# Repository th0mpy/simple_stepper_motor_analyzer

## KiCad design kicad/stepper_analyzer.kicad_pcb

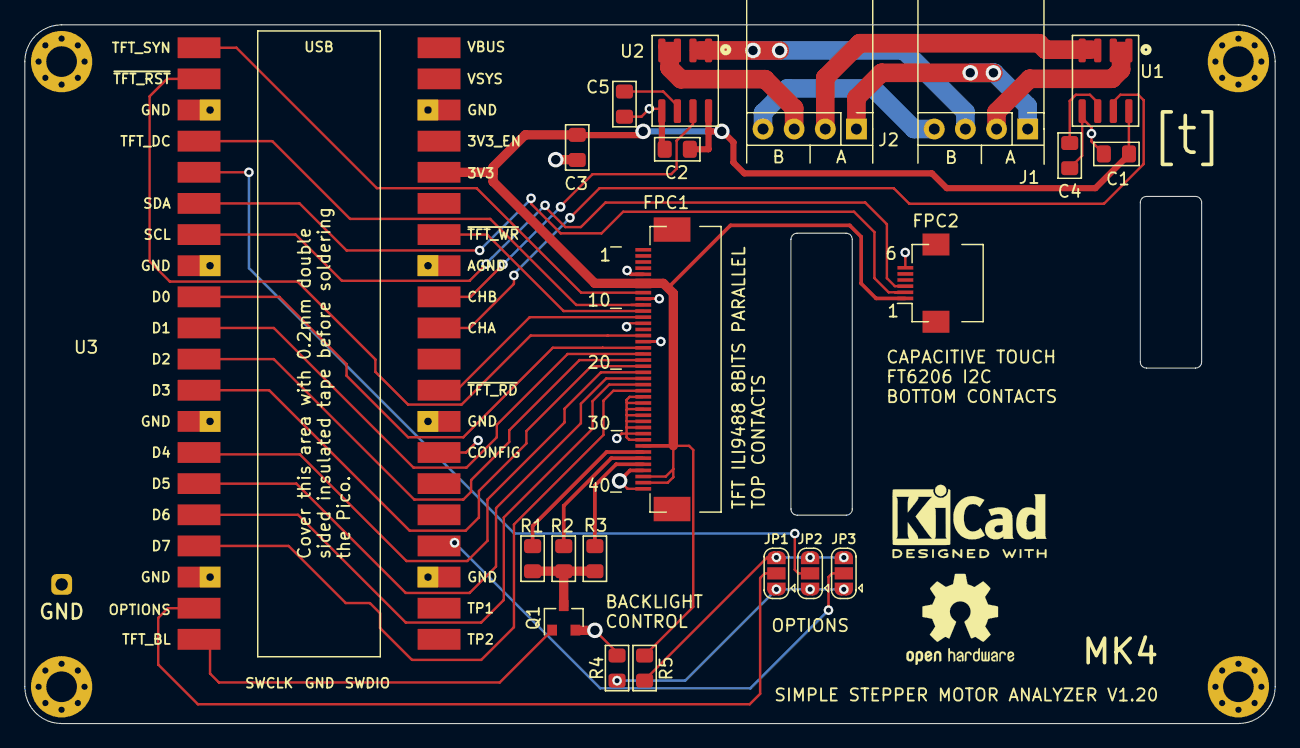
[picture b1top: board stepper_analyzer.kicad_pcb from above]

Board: 2 copper layers, 102.0 x 57.0 mm, 28 parts (1 on the bottom side), 37 nets.

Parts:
C1, C2: 0.1u; C_0805_2012Metric_Pad1.15x1.40mm_HandSolder
C3: 10u; C_0805_2012Metric_Pad1.15x1.40mm_HandSolder
C4: 1nf; C_0805_2012Metric_Pad1.15x1.40mm_HandSolder
C5: DNP; C_0805_2012Metric_Pad1.15x1.40mm_HandSolder
FPC1: Connector_Conn_01x40_Female; JUSHUO-AFC07-S40ECC-00_40P_05mm_flipped
FPC2: FPC connector, 6 pins, 0.5mm, BOTTOM contacts; JUSHUO-AFC01-S06FCC-00_6p_05mm
H1, H2, H3, H4: MountingHole; MountingHole_2.5mm_Pad_Via
J1, J2: Connector_Conn_01x04_Male; connector_4pins_horizontal
JP1: OPTION1; SolderJumper-3_P1.3mm_Open_RoundedPad1.0x1.5mm
JP2: OPTION2; SolderJumper-3_P1.3mm_Open_RoundedPad1.0x1.5mm
JP3: OPTION3; SolderJumper-3_P1.3mm_Open_RoundedPad1.0x1.5mm
LOGO1: Logo_Open_Hardware_Small; OSHW-Logo2_9.8x8mm_SilkScreen
M1: Motor; null_footprint
Q1: AO3400A; SOT-23
R1, R2, R3: 8R2; R_0805_2012Metric_Pad1.15x1.40mm_HandSolder
R4: 1K; R_0805_2012Metric_Pad1.15x1.40mm_HandSolder
R5: 1K; R_0805_2012Metric_Pad1.15x1.40mm_HandSolder_no_3d
TP3: TestPoint; testpoint_double_side
U1, U2: (CURRENT SENSOR); SOIC-8_3.9x4.9mm_P1.27mm
U3: Pico; Pico_smd_dedicated

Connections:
+3V3: C1.2, C2.2, C3.2, FPC1.6, FPC1.7, FPC1.33, FPC1.38, FPC1.39, FPC2.1, R5.2, U1.8, U2.8, U3.36
/CHA: U1.7, U3.31
/CHB: U2.7, U3.32
/D0: FPC1.17, U3.9
/D1: FPC1.18, U3.10
/D2: FPC1.19, U3.11
/D3: FPC1.20, U3.12
/D4: FPC1.21, U3.14
/D5: FPC1.22, U3.15
/D6: FPC1.23, U3.16
/D7: FPC1.24, U3.17
/OPTION1: JP1.2, U3.19
/OPTION2: JP2.2, U3.5
/OPTION3: JP3.2, U3.24
/SCL: FPC2.3, U3.7
/SDA: FPC2.2, U3.6
/TFT_BL: Q1.1, U3.20
/TFT_DC: FPC1.10, U3.4
/TFT_SYN: FPC1.8, U3.1
/~TFT_RD: FPC1.12, U3.29
/~TFT_RST: FPC1.15, U3.2
/~TFT_WR: FPC1.11, U3.34
GND: C1.1, C2.1, C3.1, C4.1, C5.1, FPC1.5, FPC1.9, FPC1.13, FPC1.16, FPC1.25, FPC1.26, FPC1.27, FPC1.28, FPC1.29, FPC1.30, FPC1.31, FPC1.32, FPC1.37, FPC1.40, FPC2.6, Q1.2, R4.2, TP3.1, U1.5, U2.5, U3.3, U3.8, U3.13, U3.18, U3.23, U3.27, U3.28, U3.33, U3.38
unnamed: C4.2, U1.6
unnamed: C5.2, U2.6
unnamed: FPC1.34, R1.2
unnamed: FPC1.35, R2.2
unnamed: FPC1.36, R3.2
unnamed: J1.1, J2.1
unnamed: J1.2, U1.1, U1.2
unnamed: J1.3, U2.1, U2.2
unnamed: J1.4, J2.4
unnamed: J2.2, U1.3, U1.4
unnamed: J2.3, U2.3, U2.4
unnamed: JP1.1, JP2.1, JP3.1, R4.1
unnamed: JP1.3, JP2.3, JP3.3, R5.1
unnamed: Q1.3, R1.1, R2.1, R3.1

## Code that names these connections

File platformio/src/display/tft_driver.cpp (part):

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namespace tft_driver {

// Plain GPIO output pins.
#define TFT_RST_PIN 1  // Active low.
#define TFT_DC_PIN 2   // 1: data, 0: command.
#define TFT_BL_PIN 15  // Active high

// Outputs managed by PioTft.
#define TFT_D0_PIN 6   // First of 8 data pins, [GPIO_6, GPIO_13]
#define TFT_WR_PIN 28  // Active low
// Added in MK4. Prior versions cannot read the TFT.
#define TFT_RD_PIN 22  // Active low

#define TFT_RST_HIGH gpio_set_mask(1ul << TFT_RST_PIN)
#define TFT_DC_HIGH gpio_set_mask(1ul << TFT_DC_PIN)

#define TFT_RST_LOW gpio_clr_mask(1ul << TFT_RST_PIN)
#define TFT_DC_LOW gpio_clr_mask(1ul << TFT_DC_PIN)

// // Assuming landscape mode per memory access command 0x36.
#define WIDTH 480
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
// BL output is PWM driven.
static void init_pwm() {
  bl_pwm_slice_num = pwm_gpio_to_slice_num(TFT_BL_PIN);
  bl_pwm_channel = pwm_gpio_to_channel(TFT_BL_PIN);
  gpio_set_function(TFT_BL_PIN, GPIO_FUNC_PWM);
  pwm_set_wrap(bl_pwm_slice_num, 99);
  //pwm_set_wrap(bl_pwm_slice_num, 25);
  // Reduce PWM freq to ~4.8Khz
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
static void init_gpio() {
  // A mask with all gpio output pins we use.
  constexpr uint kOutputMask = 1ul << TFT_RST_PIN | 1ul << TFT_DC_PIN;
  gpio_init_mask(kOutputMask);
  gpio_set_dir_out_masked(kOutputMask);
}
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  pio_program_offset = pio_add_program(PIO, &tft_driver_pio_program);

  // Associate pins with the PIO.
  pio_gpio_init(PIO, TFT_WR_PIN);
  pio_gpio_init(PIO, TFT_RD_PIN);
  for (int i = 0; i < 8; i++) {
    pio_gpio_init(PIO, TFT_D0_PIN + i);
  }

  // Configure the pins to be outputs.
  pio_sm_set_consecutive_pindirs(PIO, SM, TFT_WR_PIN, 1, true);
  pio_sm_set_consecutive_pindirs(PIO, SM, TFT_RD_PIN, 1, true);
  // Initially outputs. The PIO program latter toggle these to be
  // input or output as needed.
  pio_sm_set_consecutive_pindirs(PIO, SM, TFT_D0_PIN, 8, true);
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      tft_driver_pio_program_get_default_config(pio_program_offset);
  // The pio program declares that a single sideset pin is used.
  // Define it.
  sm_config_set_sideset_pins(&c, TFT_WR_PIN);
  sm_config_set_set_pins(&c, TFT_RD_PIN, 1);

  // The 8 consecutive pins that are used for data outout.
  sm_config_set_out_pins(&c, TFT_D0_PIN, 8);
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
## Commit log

2022-12-17 Update before Etsy
    Updated code and hardware for Th0mpy's version of the analyzer
